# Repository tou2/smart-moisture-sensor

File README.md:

# Smart Moisture Sensor

A pencil-shaped, battery-powered Bluetooth Low Energy soil probe. You push the pointed end into the soil. Electrodes on that end measure soil moisture capacitively. The part that stays above ground measures air temperature, humidity, pressure and light, and reports the readings over BLE.

The hardware is designed in **KiCad 10**, with parts chosen for **JLCPCB** assembly.

> **Status:** schematic done. Footprints are placed and the zones are defined, but the board is **not routed yet**. There is no firmware in this repo yet.

## Board at a glance

- **Outline:** 20 × 172 mm, 2 layers. The board narrows to a point starting at y = 150 mm.
- **Layout, from the top of the board to the tip:**

  ```
  ┌──────────┐  0 mm
  │ antenna  │  chip antenna + copper keep-out (0–5 mm)
  │ nRF52832 │  MCU, 32 MHz / 32.768 kHz crystals, RF match, DC/DC filter
  │ ○○○○○    │  test pads: SWDIO, SWDCLK, RESET, 3V3, GND
  │ sensors  │  SHT40 · MS5607 · OPT3004
  │ buzzer   │  piezo
  │ power    │  TPS610994 boost, status LED
  │          │
  │ AAA cell │  battery holder
  │          │
  ├──────────┤  128 mm: soil line
  │ ▌ █ ▐    │  electrodes: sense plate between GND guard strips
  │  \  /    │
  └───\/─────┘  172 mm: tip
  ```

## Main components

| Ref | Part | Function | LCSC |
|-----|------|----------|------|
| U1 | nRF52832-QFAA | BLE SoC (Cortex-M4F) | C77540 |
| U2 | TPS610994YFFR | Boost converter, 0.7–5.5 V in → 3.3 V | C2650335 |
| U3 | SHT40-AD1B | Temperature and humidity (I²C) | C2909890 |
| U4 | MS560702BA03 | Barometric pressure (I²C) | C97627 |
| U5 | OPT3004DNPR | Ambient light (I²C, interrupt on `LIGHT_INT`) | C2655153 |
| AE1 | 2450AT42A100E | 2.4 GHz chip antenna | C2917719 |
| Y1 | X201632MKB4SI | 32 MHz crystal | C718072 |
| Y2 | Q13FC13500004 | 32.768 kHz crystal | C32346 |
| BZ1 | PKLCS1212E4001 | 4 kHz piezo buzzer, driven differentially | C113159 |
| L1 | APH0420T1R0M | 1 µH boost inductor | C5349664 |
| BT1 | BH-AAA-B5AA001 | AAA battery holder | C964881 |
| D1 | Green LED | Status LED | n/a |

The board runs from a single AAA cell. U2 boosts the cell voltage to 3V3 for everything else. The nRF52832's internal DC/DC regulator is used (L2 and L3 on `DCC`/`DEC4`).

### Moisture measurement

The sense plate (`MOIST_SNS`) and the GND guard strips on each side form a capacitor. Soil moisture changes its capacitance. The same electrode pattern is on both copper layers, so the probe senses soil on both faces.

- `MOIST_DRV` (GPIO) charges the plate through R2 (1 MΩ).
- `MOIST_AIN` (SAADC input) reads the plate voltage through R3 (1 kΩ).

The charge time (RC) indicates the moisture level. The electrodes stay **under solder mask**, so no bare copper touches the soil.

## Repository layout

```
moisture-probe/            KiCad project
  moisture-probe.kicad_sch   schematic
  moisture-probe.kicad_pcb   PCB
  libs/                      JLCPCB/LCSC symbols (C*.kicad_sym) and footprints (kicad_jlcpcb.pretty)
tools/
  layout_probe.py          pcbnew script: board outline, placement, zones
```

## Regenerating the layout

[tools/layout_probe.py](tools/layout_probe.py) takes the board produced by the JLCPCB plugin and turns it into the probe. The script:

- replaces the outline with the pencil shape
- places every footprint at fixed coordinates
- adds the antenna keep-out, the GND pours and the electrode zones
- fills the zones

You can run it more than once safely. It has to run with KiCad's bundled Python, because `pcbnew` is only importable there:

```sh
"C:/Program Files/KiCad/10.0/bin/python.exe" tools/layout_probe.py moisture-probe/moisture-probe.kicad_pcb
```

Close the board in KiCad before you run it, then reopen it afterwards. To move a part, edit the `PLACEMENT` table at the top of the script.

## Next steps

- [ ] Route the board and pass DRC
- [ ] Generate the BOM and CPL files for JLCPCB assembly
- [ ] Write the firmware: BLE advertising, sensor drivers, moisture calibration
- [ ] Design an enclosure or conformal coating for the electronics above the soil line

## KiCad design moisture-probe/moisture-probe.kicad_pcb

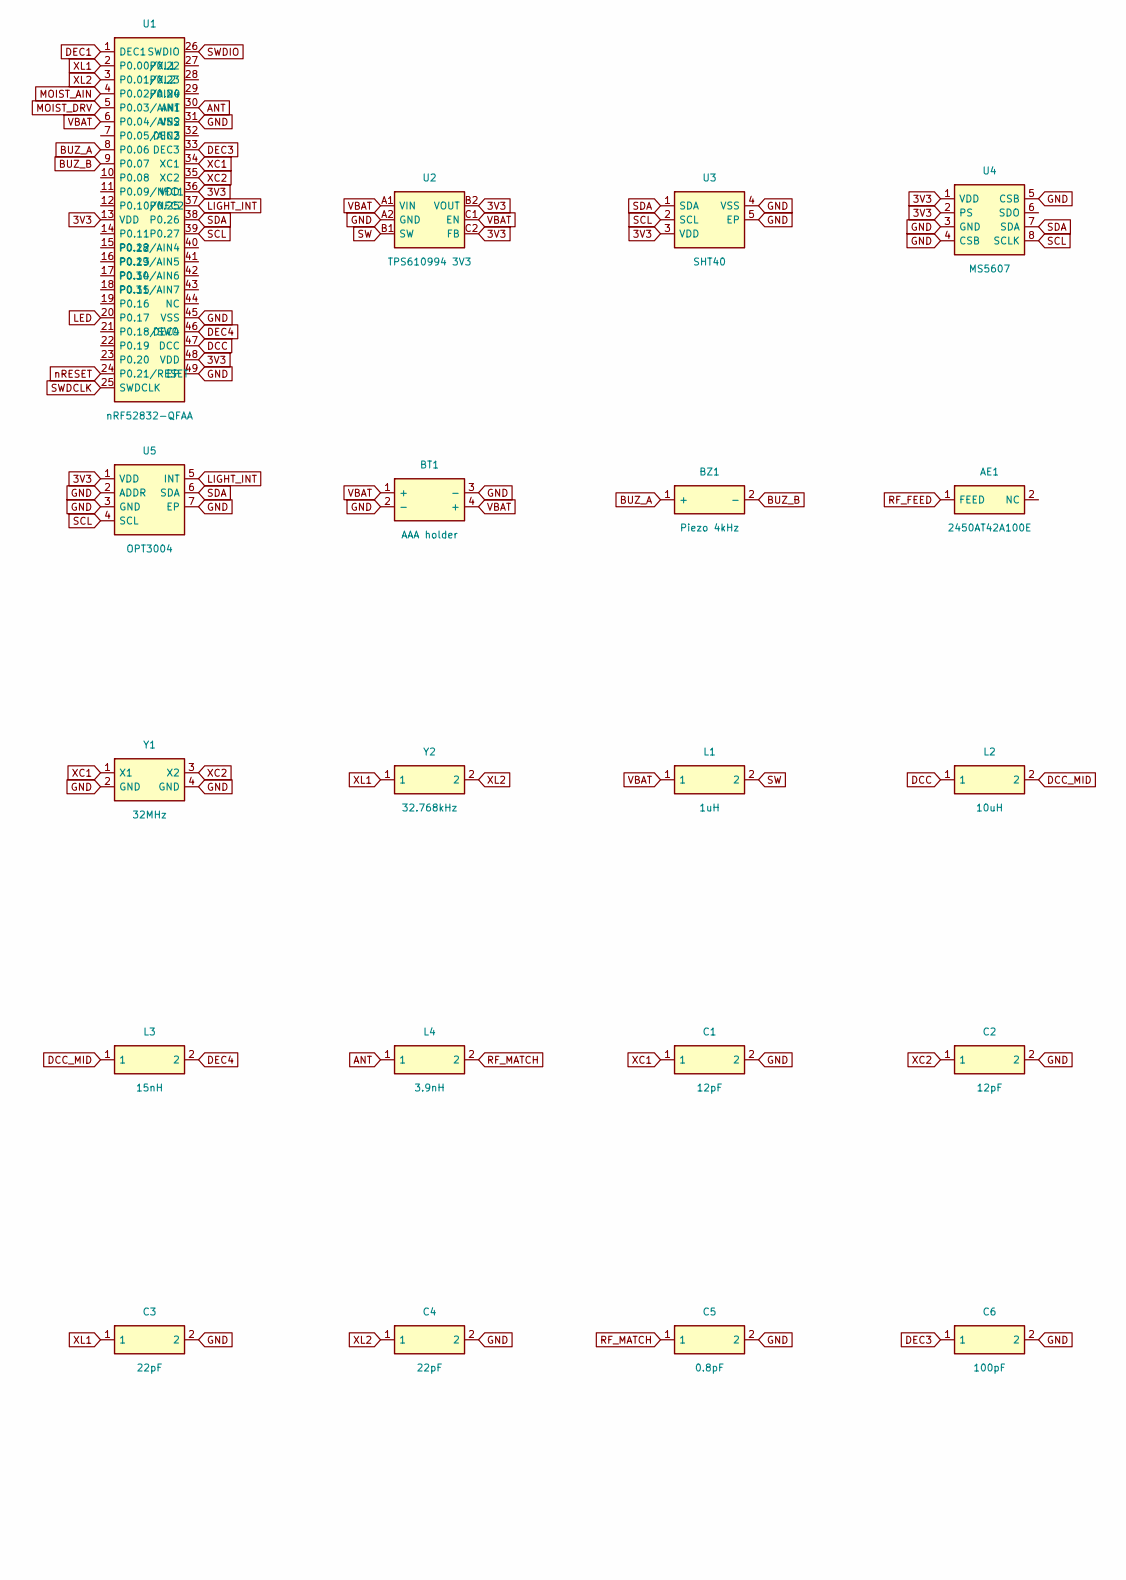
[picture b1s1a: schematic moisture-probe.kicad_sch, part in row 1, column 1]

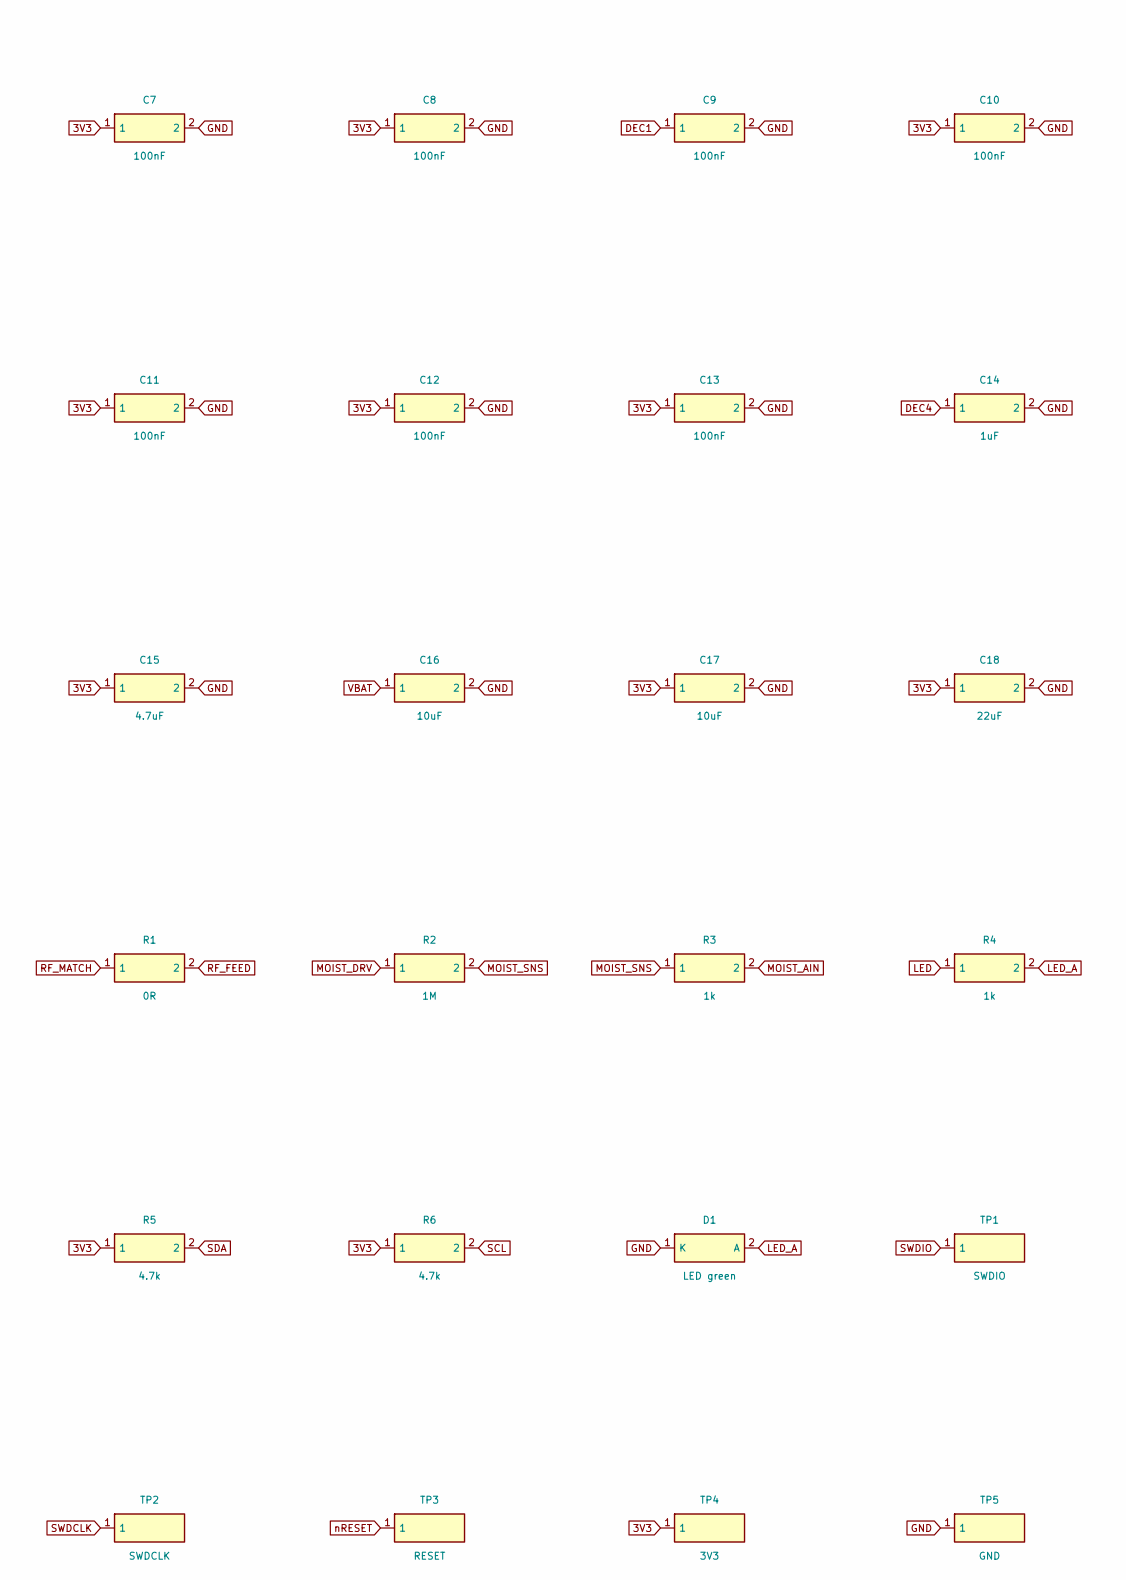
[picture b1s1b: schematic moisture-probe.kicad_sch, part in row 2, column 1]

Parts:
AE1: 2450AT42A100E; C2917719_SMD_5x2mm; LCSC C2917719
BT1: AAA holder; C964881_-; LCSC C964881
BZ1: Piezo 4kHz; C113159_SMD_12x12mm; LCSC C113159
C1, C2: 12pF; C_0402_1005Metric; LCSC C1547
C3, C4: 22pF; C_0402_1005Metric; LCSC C1555
C5: 0.8pF; C_0402_1005Metric; LCSC C327032
C6: 100pF; C_0402_1005Metric; LCSC C1546
C7, C8, C9, C10, C11, C12, C13: 100nF; C_0402_1005Metric; LCSC C1525
C14: 1uF; C_0603_1608Metric; LCSC C15849
C15: 4.7uF; C_0603_1608Metric; LCSC C19666
C16, C17: 10uF; C_0603_1608Metric; LCSC C19702
C18: 22uF; C_0805_2012Metric; LCSC C45783
D1: LED green; LED_0603_1608Metric; LCSC C965806
L1: 1uH; C5349664_SMD_4_4x4_2mm; LCSC C5349664
L2: 10uH; L_0603_1608Metric; LCSC C6807729
L3: 15nH; L_0402_1005Metric; LCSC C98055
L4: 3.9nH; L_0201_0603Metric; LCSC C918993
R1: 0R; R_0402_1005Metric; LCSC C17168
R2: 1M; R_0402_1005Metric; LCSC C26083
R3, R4: 1k; R_0402_1005Metric; LCSC C11702
R5, R6: 4.7k; R_0402_1005Metric; LCSC C25900
TP1: SWDIO; TestPoint_Pad_D1.0mm
TP2: SWDCLK; TestPoint_Pad_D1.0mm
TP3: RESET; TestPoint_Pad_D1.0mm
TP4: 3V3; TestPoint_Pad_D1.0mm
TP5: GND; TestPoint_Pad_D1.0mm
U1: nRF52832-QFAA; C77540_QFN-48-EP_6x6_; LCSC C77540
U2: TPS610994 3V3; C2650335_DSBGA-6; LCSC C2650335
U3: SHT40; C2909890_DFN-4-EP_1_5x1_5_; LCSC C2909890
U4: MS5607; C97627_SMD-8P; LCSC C97627
U5: OPT3004; C2655153_WSON-6-EP_2x2_; LCSC C2655153
Y1: 32MHz; C718072_SMD2016-4P; LCSC C718072
Y2: 32.768kHz; C32346_SMD3215-2P; LCSC C32346

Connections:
3V3: C7.1, C8.1, C10.1, C11.1, C12.1, C13.1, C15.1, C17.1, C18.1, R5.1, R6.1, TP4.1, U1.13 (VDD), U1.36 (VDD), U1.48 (VDD), U2.B2 (VOUT), U2.C2 (FB), U3.3 (VDD), U4.1 (VDD), U4.2 (PS), U5.1 (VDD)
ANT: L4.1, U1.30 (ANT)
BUZ_A: BZ1.1 (+), U1.8 (P0.06)
BUZ_B: BZ1.2 (-), U1.9 (P0.07)
DCC: L2.1, U1.47 (DCC)
DCC_MID: L2.2, L3.1
DEC1: C9.1, U1.1 (DEC1)
DEC3: C6.1, U1.33 (DEC3)
DEC4: C14.1, L3.2, U1.46 (DEC4)
GND: BT1.2 (-), BT1.3 (-), C1.2, C2.2, C3.2, C4.2, C5.2, C6.2, C7.2, C8.2, C9.2, C10.2, C11.2, C12.2, C13.2, C14.2, C15.2, C16.2, C17.2, C18.2, D1.1 (K), TP5.1, U1.31 (VSS), U1.45 (VSS), U1.49 (EP), U2.A2 (GND), U3.4 (VSS), U3.5 (EP), U4.3 (GND), U4.4 (CSB), U4.5 (CSB), U5.2 (ADDR), U5.3 (GND), U5.7 (EP), Y1.2 (GND), Y1.4 (GND)
LED: R4.1, U1.20 (P0.17)
LED_A: D1.2 (A), R4.2
LIGHT_INT: U1.37 (P0.25), U5.5 (INT)
MOIST_AIN: R3.2, U1.4 (P0.02/AIN0)
MOIST_DRV: R2.1, U1.5 (P0.03/AIN1)
MOIST_SNS: R2.2, R3.1
RF_FEED: AE1.1 (FEED), R1.2
RF_MATCH: C5.1, L4.2, R1.1
SCL: R6.2, U1.39 (P0.27), U3.2 (SCL), U4.8 (SCLK), U5.4 (SCL)
SDA: R5.2, U1.38 (P0.26), U3.1 (SDA), U4.7 (SDA), U5.6 (SDA)
SW: L1.2, U2.B1 (SW)
SWDCLK: TP2.1, U1.25 (SWDCLK)
SWDIO: TP1.1, U1.26 (SWDIO)
VBAT: BT1.1 (+), BT1.4 (+), C16.1, L1.1, U1.6 (P0.04/AIN2), U2.A1 (VIN), U2.C1 (EN)
XC1: C1.1, U1.34 (XC1), Y1.1 (X1)
XC2: C2.1, U1.35 (XC2), Y1.3 (X2)
XL1: C3.1, U1.2 (P0.00/XL1), Y2.1
XL2: C4.1, U1.3 (P0.01/XL2), Y2.2
nRESET: TP3.1, U1.24 (P0.21/RESET)

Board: 2 copper layers, 44 parts (0 on the bottom side), 29 nets, no tracks yet.
